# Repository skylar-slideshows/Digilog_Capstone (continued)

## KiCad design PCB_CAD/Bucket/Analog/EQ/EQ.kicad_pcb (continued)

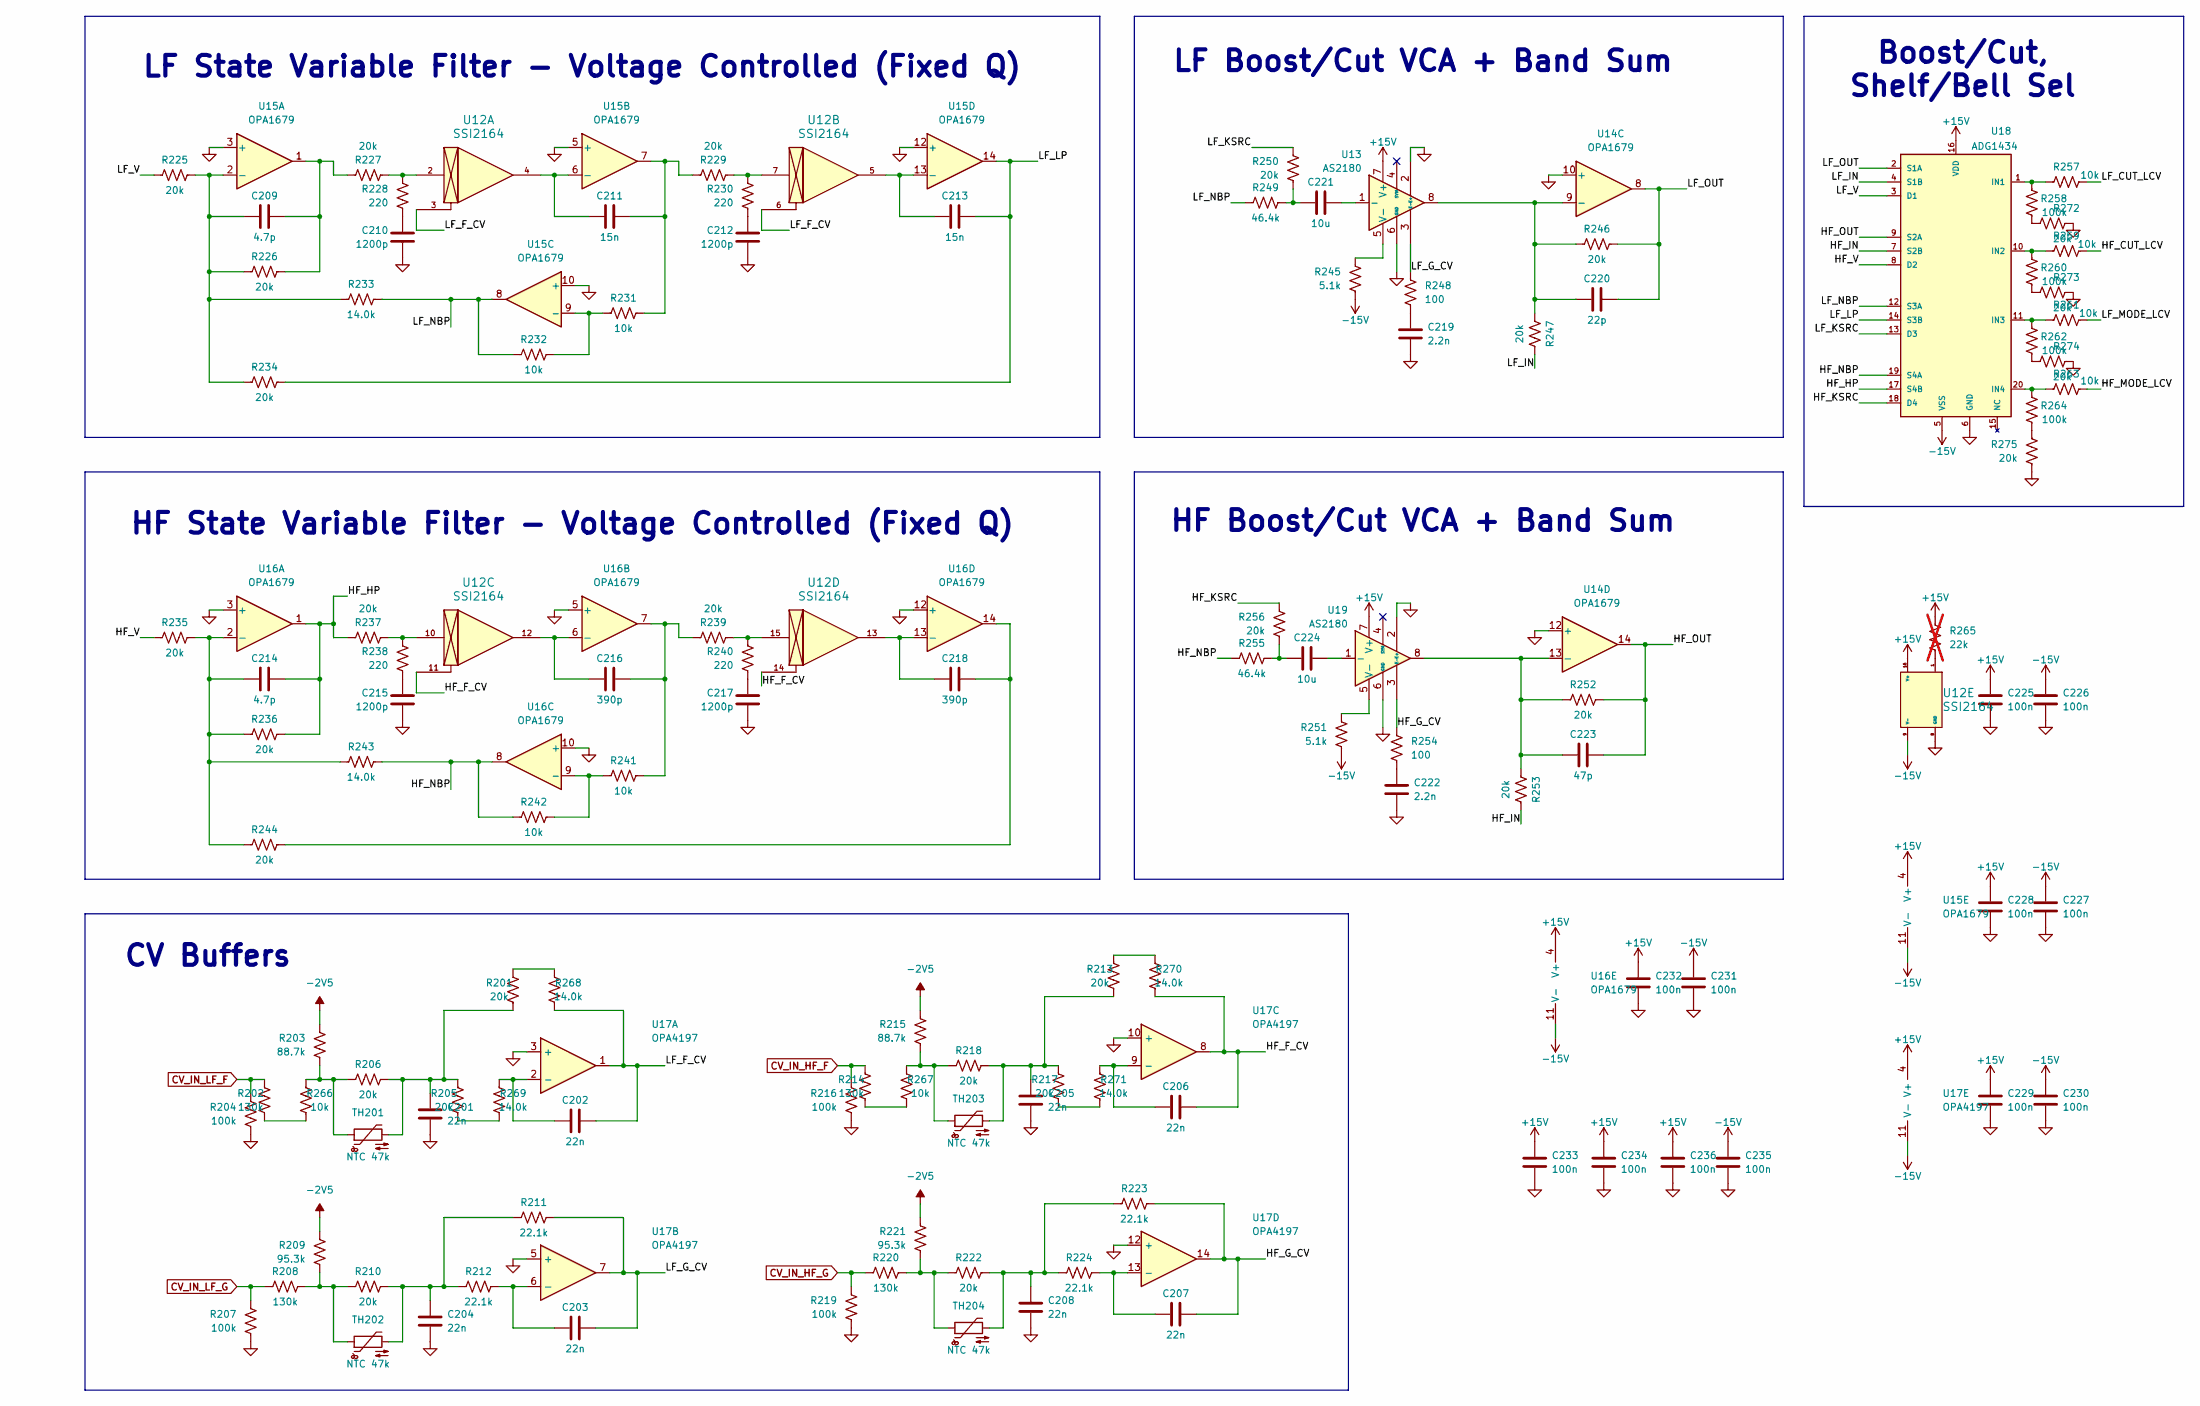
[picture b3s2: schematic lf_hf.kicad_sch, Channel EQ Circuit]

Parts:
C201, C202, C203, C204, C205, C206, C207, C208: 22n; C_Rect_L7.2mm_W2.5mm_P5.00mm; LCSC dnp
C209, C214: 4.7p; C_0603_1608Metric; LCSC C282071
C210, C212, C215, C217: 1200p; C_1206_3216Metric; LCSC C527278
C211, C213: 15n; C_Rect_L7.2mm_W2.5mm_P5.00mm; LCSC dnp
C216, C218: 390p; C_0603_1608Metric; LCSC C107050
C219, C222: 2.2n; C_0805_2012Metric; LCSC C107103
C220: 22p; C_0603_1608Metric; LCSC C105620
C221, C224: 10u; CP_Elec_6.3x5.4_Nichicon; LCSC C340735
C223: 47p; C_0603_1608Metric; LCSC C105622
C225, C226, C227, C228, C229, C230, C231, C232, C233, C234, C235, C236: 100n; C_0603_1608Metric; LCSC C1591
R201, R205, R206, R210, R213, R217, R218, R222, R225, R226, R227, R229, R234, R235, R236, R237, R239, R244, R246, R247, R250, R252, R253, R256, R272, R273, R274, R275: 20k; R_0603_1608Metric
R202, R208, R214, R220: 130k; R_0603_1608Metric
R203, R215: 88.7k; R_0603_1608Metric
R204, R207, R216, R219, R258, R260, R262, R264: 100k; R_0603_1608Metric
R209, R221: 95.3k; R_0603_1608Metric
R211, R212, R223, R224: 22.1k; R_0603_1608Metric
R228, R230, R238, R240: 220; R_0603_1608Metric
R231, R232, R241, R242, R257, R259, R261, R263, R266, R267: 10k; R_0603_1608Metric
R233, R243, R268, R269, R270, R271: 14.0k; R_0603_1608Metric
R245, R251: 5.1k; R_0603_1608Metric
R248, R254: 100; R_0603_1608Metric
R249, R255: 46.4k; R_0603_1608Metric
R265: 22k; R_0603_1608Metric; not fitted
TH201, TH202, TH203, TH204: NTC 47k; R_Axial_DIN0207_L6.3mm_D2.5mm_P2.54mm_Vertical; MPN NTCLE100E3473JB0; LCSC dnp
U12: SSI2164; SOIC-16_3.9x9.9mm_Pitch1.27mm; LCSC dnp
U13, U19: AS2180; SOIC-8-1EP_3.9x4.9mm_P1.27mm_EP2.29x3mm_ThermalVias; LCSC dnp
U14, U15, U16: OPA1679; SOIC-14_3.9x8.7mm_P1.27mm; LCSC C2057264
U17: OPA4197; SOIC-14_3.9x8.7mm_P1.27mm; LCSC C2058532
U18: ADG1434; TSSOP-20_4.4x6.5mm_P0.65mm; LCSC C408906

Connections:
+15V: C225.1, C228.1, C229.1, C232.1, C233.1, C234.1, C236.1, R265.1, U12.16 (V+), U13.7 (V+), U15.4 (V+), U16.4 (V+), U17.4 (V+), U18.16 (VDD), U19.7 (V+); also elsewhere on the board
-2V5: R203.1, R209.1, R215.1, R221.1; also elsewhere on the board
-15V: C226.1, C227.1, C230.1, C231.1, C235.1, R245.2, R251.2, U12.9 (V-), U15.11 (V-), U16.11 (V-), U17.11 (V-), U18.5 (VSS); also elsewhere on the board
/LF_HF/HF_CUT_LCV: R259.2
/LF_HF/HF_F_CV: C206.2, R270.2, U12.11, U12.14, U17.8
/LF_HF/HF_G_CV: C207.2, R223.2, R254.1, U17.14, U19.3 (E-)
/LF_HF/HF_HP: C214.2, R236.2, R237.1, U16.1, U18.17 (S4B)
/LF_HF/HF_IN: R253.2, U18.7 (S2B)
/LF_HF/HF_KSRC: R256.1, U18.18 (D4)
/LF_HF/HF_MODE_LCV: R263.2
/LF_HF/HF_NBP: R242.1, R243.2, R255.1, U16.8, U18.19 (S4A)
/LF_HF/HF_OUT: C223.2, R252.2, U14.14, U18.9 (S2A)
/LF_HF/HF_V: R235.1, U18.8 (D2)
/LF_HF/LF_CUT_LCV: R257.2
/LF_HF/LF_F_CV: C202.2, R268.2, U12.3, U12.6, U17.1
/LF_HF/LF_G_CV: C203.2, R211.2, R248.1, U13.3 (E-), U17.7
/LF_HF/LF_IN: R247.2, U18.4 (S1B)
/LF_HF/LF_KSRC: R250.1, U18.13 (D3)
/LF_HF/LF_LP: C213.2, R234.2, U15.14, U18.14 (S3B)
/LF_HF/LF_MODE_LCV: R261.2
/LF_HF/LF_NBP: R232.1, R233.2, R249.1, U15.8, U18.12 (S3A)
/LF_HF/LF_OUT: C220.2, R246.2, U14.8, U18.2 (S1A)
/LF_HF/LF_V: R225.1, U18.3 (D1)
CV_IN_HF_F: R214.1, R216.1
CV_IN_HF_G: R219.1, R220.1
CV_IN_LF_F: R202.1, R204.1
CV_IN_LF_G: R207.1, R208.1
GND: C201.2, C204.2, C205.2, C208.2, C210.2, C212.2, C215.2, C217.2, C219.2, C222.2, C225.2, C226.2, C227.2, C228.2, C229.2, C230.2, C231.2, C232.2, C233.2, C234.2, C235.2, C236.2, R204.2, R207.2, R216.2, R219.2, R272.2, R273.2, R274.2, R275.2, U12.8 (GND), U13.2 (E+), U13.6 (GND), U14.10 (+), U14.12 (+), U15.3 (+), U15.5 (+), U15.10 (+), U15.12 (+), U16.3 (+), U16.5 (+), U16.10 (+), U16.12 (+), U17.3 (+), U17.5 (+), U17.10 (+), U17.12 (+), U18.6 (GND), U19.2 (E+), U19.6 (GND); also elsewhere on the board
unnamed: C201.1, R201.1, R205.1, R206.2, TH201.2
unnamed: C204.1, R210.2, R211.1, R212.1, TH202.2
unnamed: C205.1, R213.1, R217.1, R218.2, TH203.2
unnamed: C208.1, R222.2, R223.1, R224.1, TH204.2
unnamed: C209.2, R226.2, R227.1, U15.1
unnamed: C210.1, R228.2
unnamed: C211.2, R229.1, R231.2, U15.7
unnamed: C212.1, R230.2
unnamed: C215.1, R238.2
unnamed: C216.2, R239.1, R241.2, U16.7
unnamed: C217.1, R240.2
unnamed: C218.2, R244.2, U16.14
unnamed: C219.1, R248.2
unnamed: C221.1, R249.2, R250.2
unnamed: C222.1, R254.2
unnamed: C224.1, R255.2, R256.2
unnamed: R201.2, R268.1
unnamed: R202.2, R266.1
unnamed: R203.2, R206.1, R266.2, TH201.1
unnamed: R205.2, R269.1
unnamed: R208.2, R209.2, R210.1, TH202.1
unnamed: R213.2, R270.1
unnamed: R214.2, R267.1
unnamed: R215.2, R218.1, R267.2, TH203.1
unnamed: R217.2, R271.1
unnamed: R220.2, R221.2, R222.1, TH204.1
unnamed: R227.2, R228.1, U12.2
unnamed: R229.2, R230.1, U12.7
unnamed: R237.2, R238.1, U12.10
unnamed: R239.2, R240.1, U12.15
unnamed: R258.2, R272.1
unnamed: R260.2, R273.1
unnamed: R262.2, R274.1
unnamed: R264.2, R275.1
unnamed: R265.2, U12.1
unnamed: C221.2, U13.1 (-)
unnamed: R245.1, U13.5 (V-)
unnamed: C220.1, R246.1, R247.1, U13.8, U14.9 (-)
unnamed: C223.1, R252.1, R253.1, U14.13 (-), U19.8
unnamed: C209.1, R225.2, R226.1, R233.1, R234.1, U15.2 (-)
unnamed: C211.1, U12.4, U15.6 (-)
unnamed: R231.1, R232.2, U15.9 (-)
unnamed: C213.1, U12.5, U15.13 (-)
unnamed: C214.1, R235.2, R236.1, R243.1, R244.1, U16.2 (-)
unnamed: C216.1, U12.12, U16.6 (-)
unnamed: R241.1, R242.2, U16.9 (-)
unnamed: C218.1, U12.13, U16.13 (-)
unnamed: C202.1, R269.2, U17.2 (-)
unnamed: C203.1, R212.2, U17.6 (-)
unnamed: C206.1, R271.2, U17.9 (-)
unnamed: C207.1, R224.2, U17.13 (-)
unnamed: R257.1, R258.1, U18.1 (IN1)
unnamed: R259.1, R260.1, U18.10 (IN2)
unnamed: R261.1, R262.1, U18.11 (IN3)
unnamed: R263.1, R264.1, U18.20 (IN4)
unnamed: C224.2, U19.1 (-)
unnamed: R251.1, U19.5 (V-)

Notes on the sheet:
LF Boost/Cut VCA + Band Sum
LF State Variable Filter - Voltage Controlled (Fixed Q)
HF Boost/Cut VCA + Band Sum
HF State Variable Filter - Voltage Controlled (Fixed Q)
Boost/Cut, Shelf/Bell Sel
CV Buffers

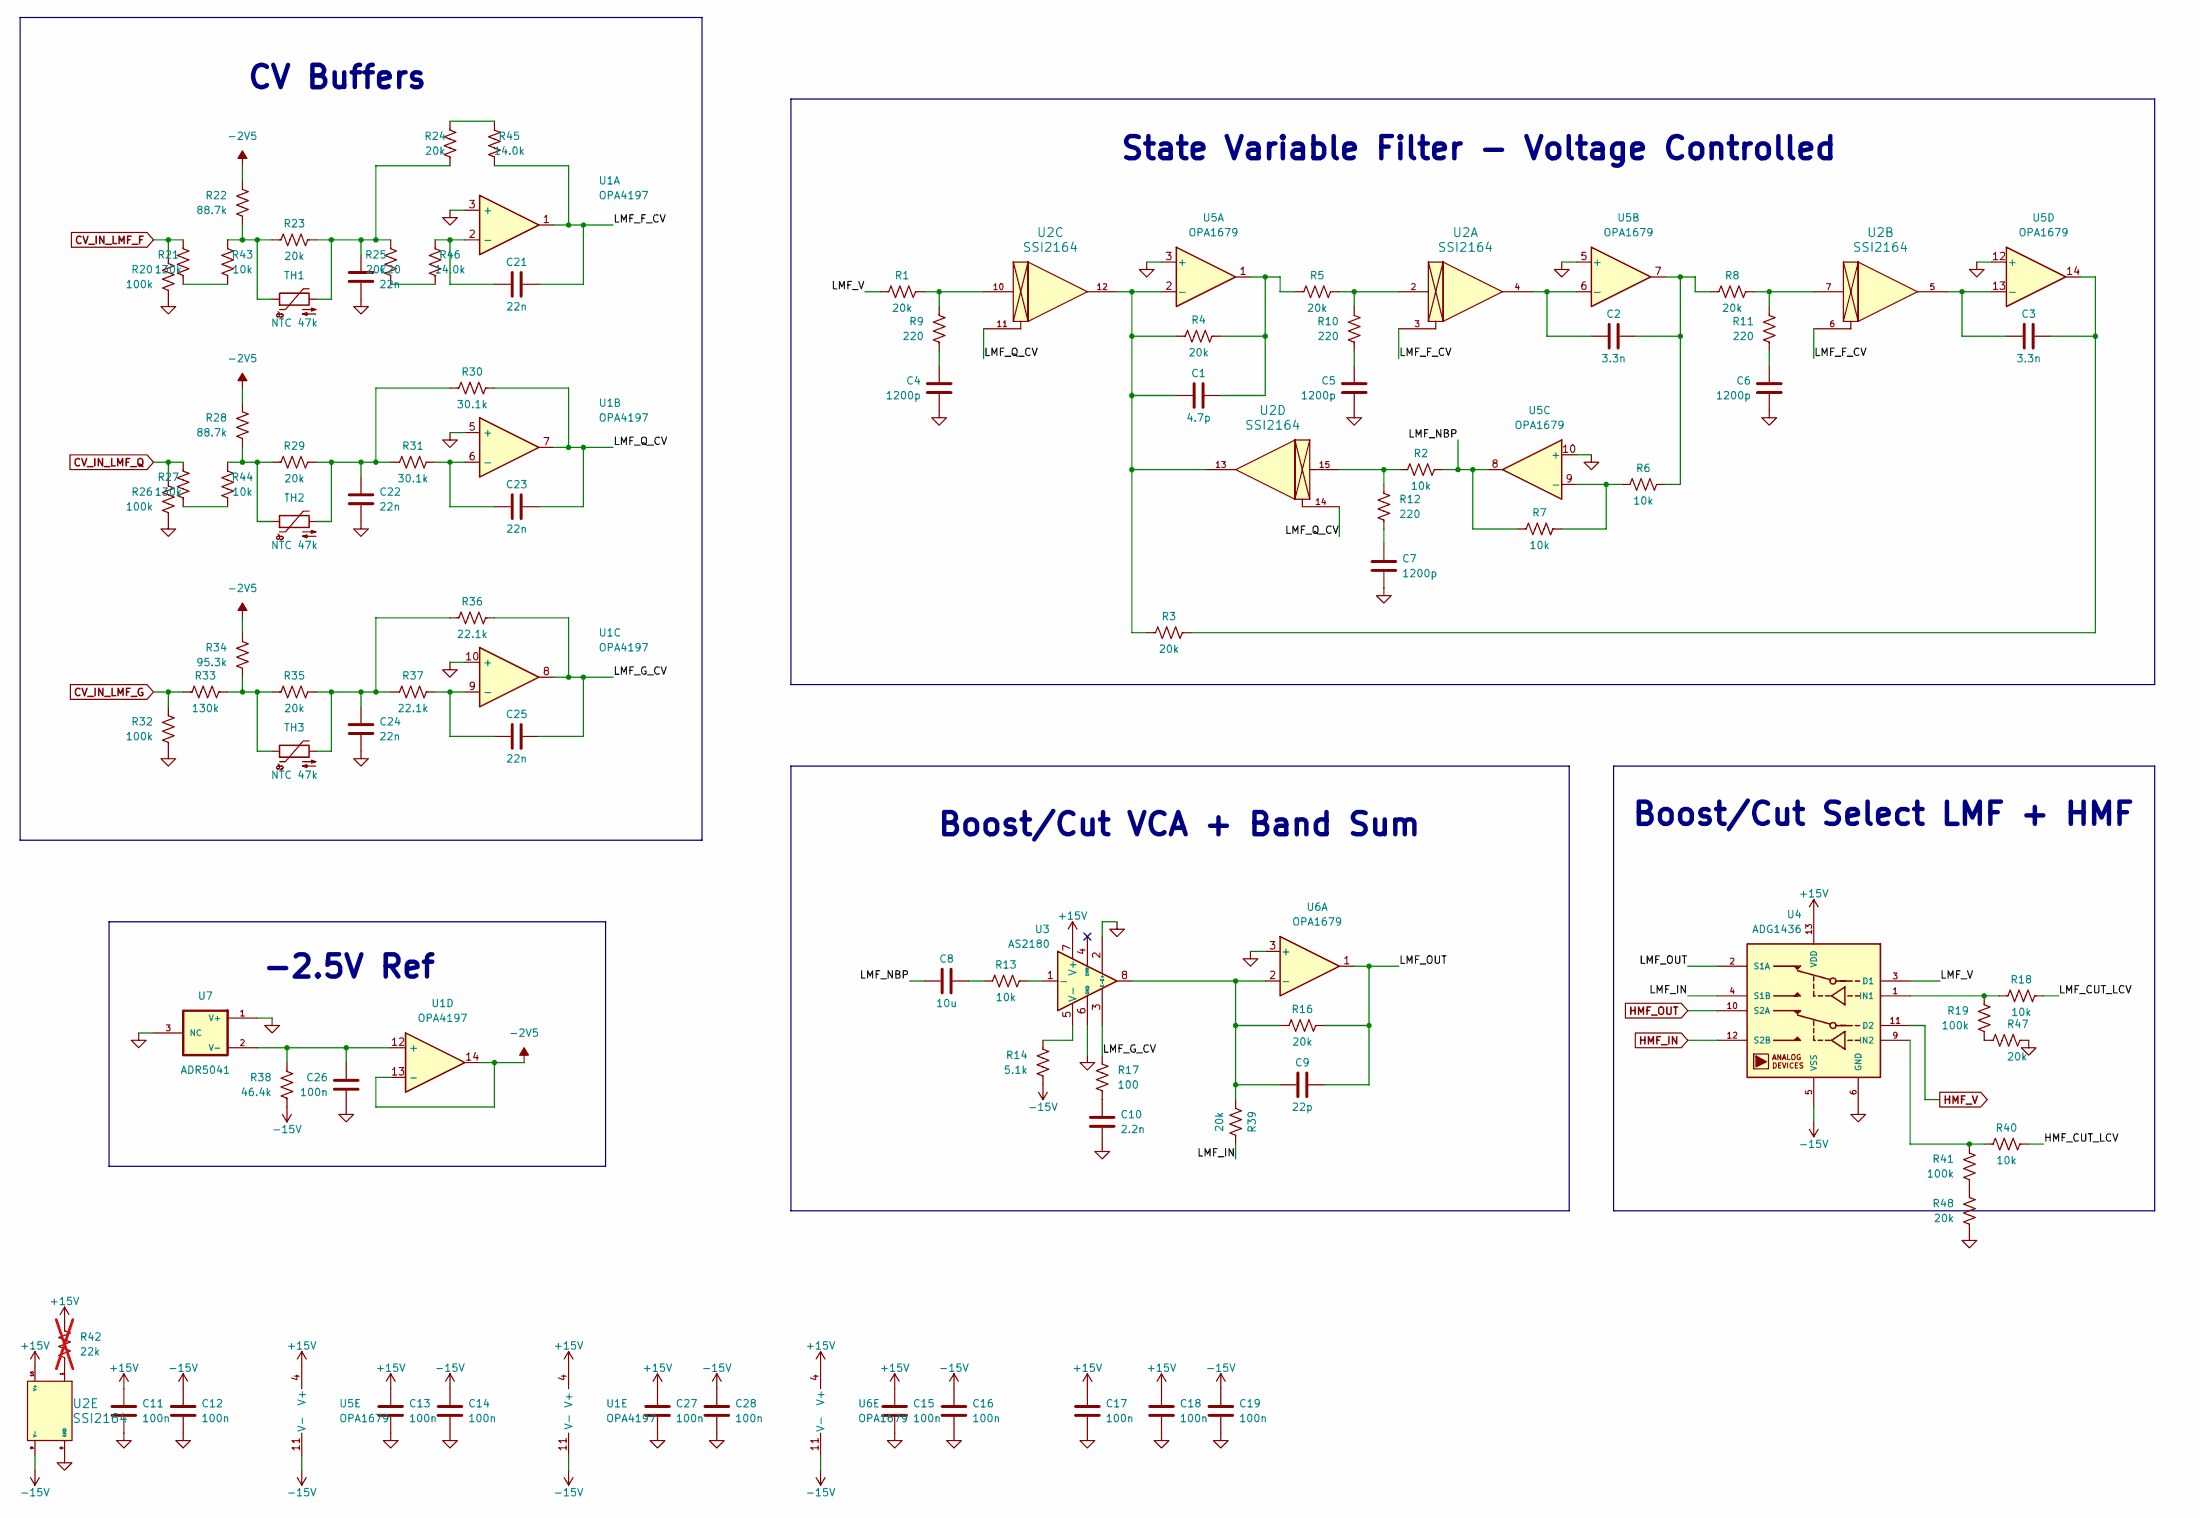
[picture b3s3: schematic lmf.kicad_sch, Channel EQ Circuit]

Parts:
C1: 4.7p; C_0603_1608Metric; LCSC C282071
C2, C3: 3.3n; C_0603_1608Metric; LCSC C107048
C4, C5, C6, C7: 1200p; C_1206_3216Metric; LCSC C527278
C8: 10u; CP_Elec_6.3x5.4_Nichicon; LCSC C340735
C9: 22p; C_0603_1608Metric; LCSC C105620
C10: 2.2n; C_0805_2012Metric; LCSC C107103
C11, C12, C13, C14, C15, C16, C17, C18, C19, C27, C28: 100n; C_0603_1608Metric; LCSC C1591
C20, C21, C22, C23, C24, C25: 22n; C_Rect_L7.2mm_W2.5mm_P5.00mm; LCSC dnp
C26: 100n; C_0603_1608Metric; LCSC C1590
R1, R3, R4, R5, R8, R16, R23, R24, R25, R29, R35, R39, R47, R48: 20k; R_0603_1608Metric
R2, R6, R7, R13, R18, R40, R43, R44: 10k; R_0603_1608Metric
R9, R10, R11, R12: 220; R_0603_1608Metric
R14: 5.1k; R_0603_1608Metric
R17: 100; R_0603_1608Metric
R19, R20, R26, R32, R41: 100k; R_0603_1608Metric
R21, R27, R33: 130k; R_0603_1608Metric
R22, R28: 88.7k; R_0603_1608Metric
R30, R31: 30.1k; R_0603_1608Metric
R34: 95.3k; R_0603_1608Metric
R36, R37: 22.1k; R_0603_1608Metric
R38: 46.4k; R_0603_1608Metric
R42: 22k; R_0603_1608Metric; not fitted
R45, R46: 14.0k; R_0603_1608Metric
TH1, TH2, TH3: NTC 47k; R_Axial_DIN0207_L6.3mm_D2.5mm_P2.54mm_Vertical; MPN NTCLE100E3473JB0; LCSC dnp
U1: OPA4197; SOIC-14_3.9x8.7mm_P1.27mm; LCSC C2058532
U2: SSI2164; SOIC-16_3.9x9.9mm_Pitch1.27mm; LCSC dnp
U3: AS2180; SOIC-8-1EP_3.9x4.9mm_P1.27mm_EP2.29x3mm_ThermalVias; LCSC dnp
U4: ADG1436; TSSOP16; LCSC C408899
U5, U6: OPA1679; SOIC-14_3.9x8.7mm_P1.27mm; LCSC C2057264
U7: ADR5041; SOT-23; MPN ADR5041ARTZ-R2; LCSC C659596

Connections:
+15V: C11.1, C13.1, C15.1, C17.1, C18.1, C27.1, R42.1, U1.4 (V+), U2.16 (V+), U3.7 (V+), U4.13 (VDD), U5.4 (V+), U6.4 (V+); also elsewhere on the board
-2V5: R22.1, R28.1, R34.1, U1.13 (-), U1.14; also elsewhere on the board
-15V: C12.1, C14.1, C16.1, C19.1, C28.1, R14.2, R38.2, U1.11 (V-), U2.9 (V-), U4.5 (VSS), U5.11 (V-), U6.11 (V-); also elsewhere on the board
/LMF/HMF_CUT_LCV: R40.2
/LMF/LMF_CUT_LCV: R18.2
/LMF/LMF_F_CV: C21.2, R45.2, U1.1, U2.3, U2.6
/LMF/LMF_G_CV: C25.2, R17.1, R36.2, U1.8, U3.3 (E-)
/LMF/LMF_IN: R39.2, U4.4 (S1B)
/LMF/LMF_NBP: C8.1, R2.2, R7.1, U5.8
/LMF/LMF_OUT: C9.2, R16.2, U4.2 (S1A), U6.1
/LMF/LMF_Q_CV: C23.2, R30.2, U1.7, U2.11, U2.14
/LMF/LMF_V: R1.1, U4.3 (D1)
CV_IN_LMF_F: R20.1, R21.1
CV_IN_LMF_G: R32.1, R33.1
CV_IN_LMF_Q: R26.1, R27.1
GND: C4.2, C5.2, C6.2, C7.2, C10.2, C11.2, C12.2, C13.2, C14.2, C15.2, C16.2, C17.2, C18.2, C19.2, C20.2, C22.2, C24.2, C26.2, C27.2, C28.2, R20.2, R26.2, R32.2, R47.2, R48.2, U1.3 (+), U1.5 (+), U1.10 (+), U2.8 (GND), U3.2 (E+), U3.6 (GND), U4.6 (GND), U5.3 (+), U5.5 (+), U5.10 (+), U5.12 (+), U6.3 (+), U7.1 (V+), U7.3 (NC); also elsewhere on the board
unnamed: C1.2, R4.2, R5.1, U5.1
unnamed: C2.2, R6.2, R8.1, U5.7
unnamed: C3.2, R3.2, U5.14
unnamed: C4.1, R9.2
unnamed: C5.1, R10.2
unnamed: C6.1, R11.2
unnamed: C7.1, R12.2
unnamed: C8.2, R13.1
unnamed: C10.1, R17.2
unnamed: C20.1, R23.2, R24.1, R25.1, TH1.2
unnamed: C22.1, R29.2, R30.1, R31.1, TH2.2
unnamed: C24.1, R35.2, R36.1, R37.1, TH3.2
unnamed: R1.2, R9.1, U2.10
unnamed: R5.2, R10.1, U2.2
unnamed: R8.2, R11.1, U2.7
unnamed: R2.1, R12.1, U2.15
unnamed: R19.2, R47.1
unnamed: R21.2, R43.1
unnamed: R22.2, R23.1, R43.2, TH1.1
unnamed: R24.2, R45.1
unnamed: R25.2, R46.1
unnamed: R27.2, R44.1
unnamed: R28.2, R29.1, R44.2, TH2.1
unnamed: R33.2, R34.2, R35.1, TH3.1
unnamed: R41.2, R48.1
unnamed: R42.2, U2.1
unnamed: C21.1, R46.2, U1.2 (-)
unnamed: C23.1, R31.2, U1.6 (-)
unnamed: C25.1, R37.2, U1.9 (-)
unnamed: C26.1, R38.1, U1.12 (+), U7.2 (V-)
unnamed: R13.2, U3.1 (-)
unnamed: R14.1, U3.5 (V-)
unnamed: R18.1, R19.1, U4.1 (IN1)
unnamed: R40.1, R41.1, U4.9 (IN2)
unnamed: C1.1, R3.1, R4.1, U2.12, U2.13, U5.2 (-)
unnamed: C2.1, U2.4, U5.6 (-)
unnamed: R6.1, R7.2, U5.9 (-)
unnamed: C3.1, U2.5, U5.13 (-)
unnamed: C9.1, R16.1, R39.1, U3.8, U6.2 (-)

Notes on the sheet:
Boost/Cut Select LMF + HMF
Boost/Cut VCA + Band Sum
-2.5V Ref
State Variable Filter - Voltage Controlled
CV Buffers

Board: 2 copper layers, 274 parts (0 on the bottom side), 168 nets, no tracks yet.

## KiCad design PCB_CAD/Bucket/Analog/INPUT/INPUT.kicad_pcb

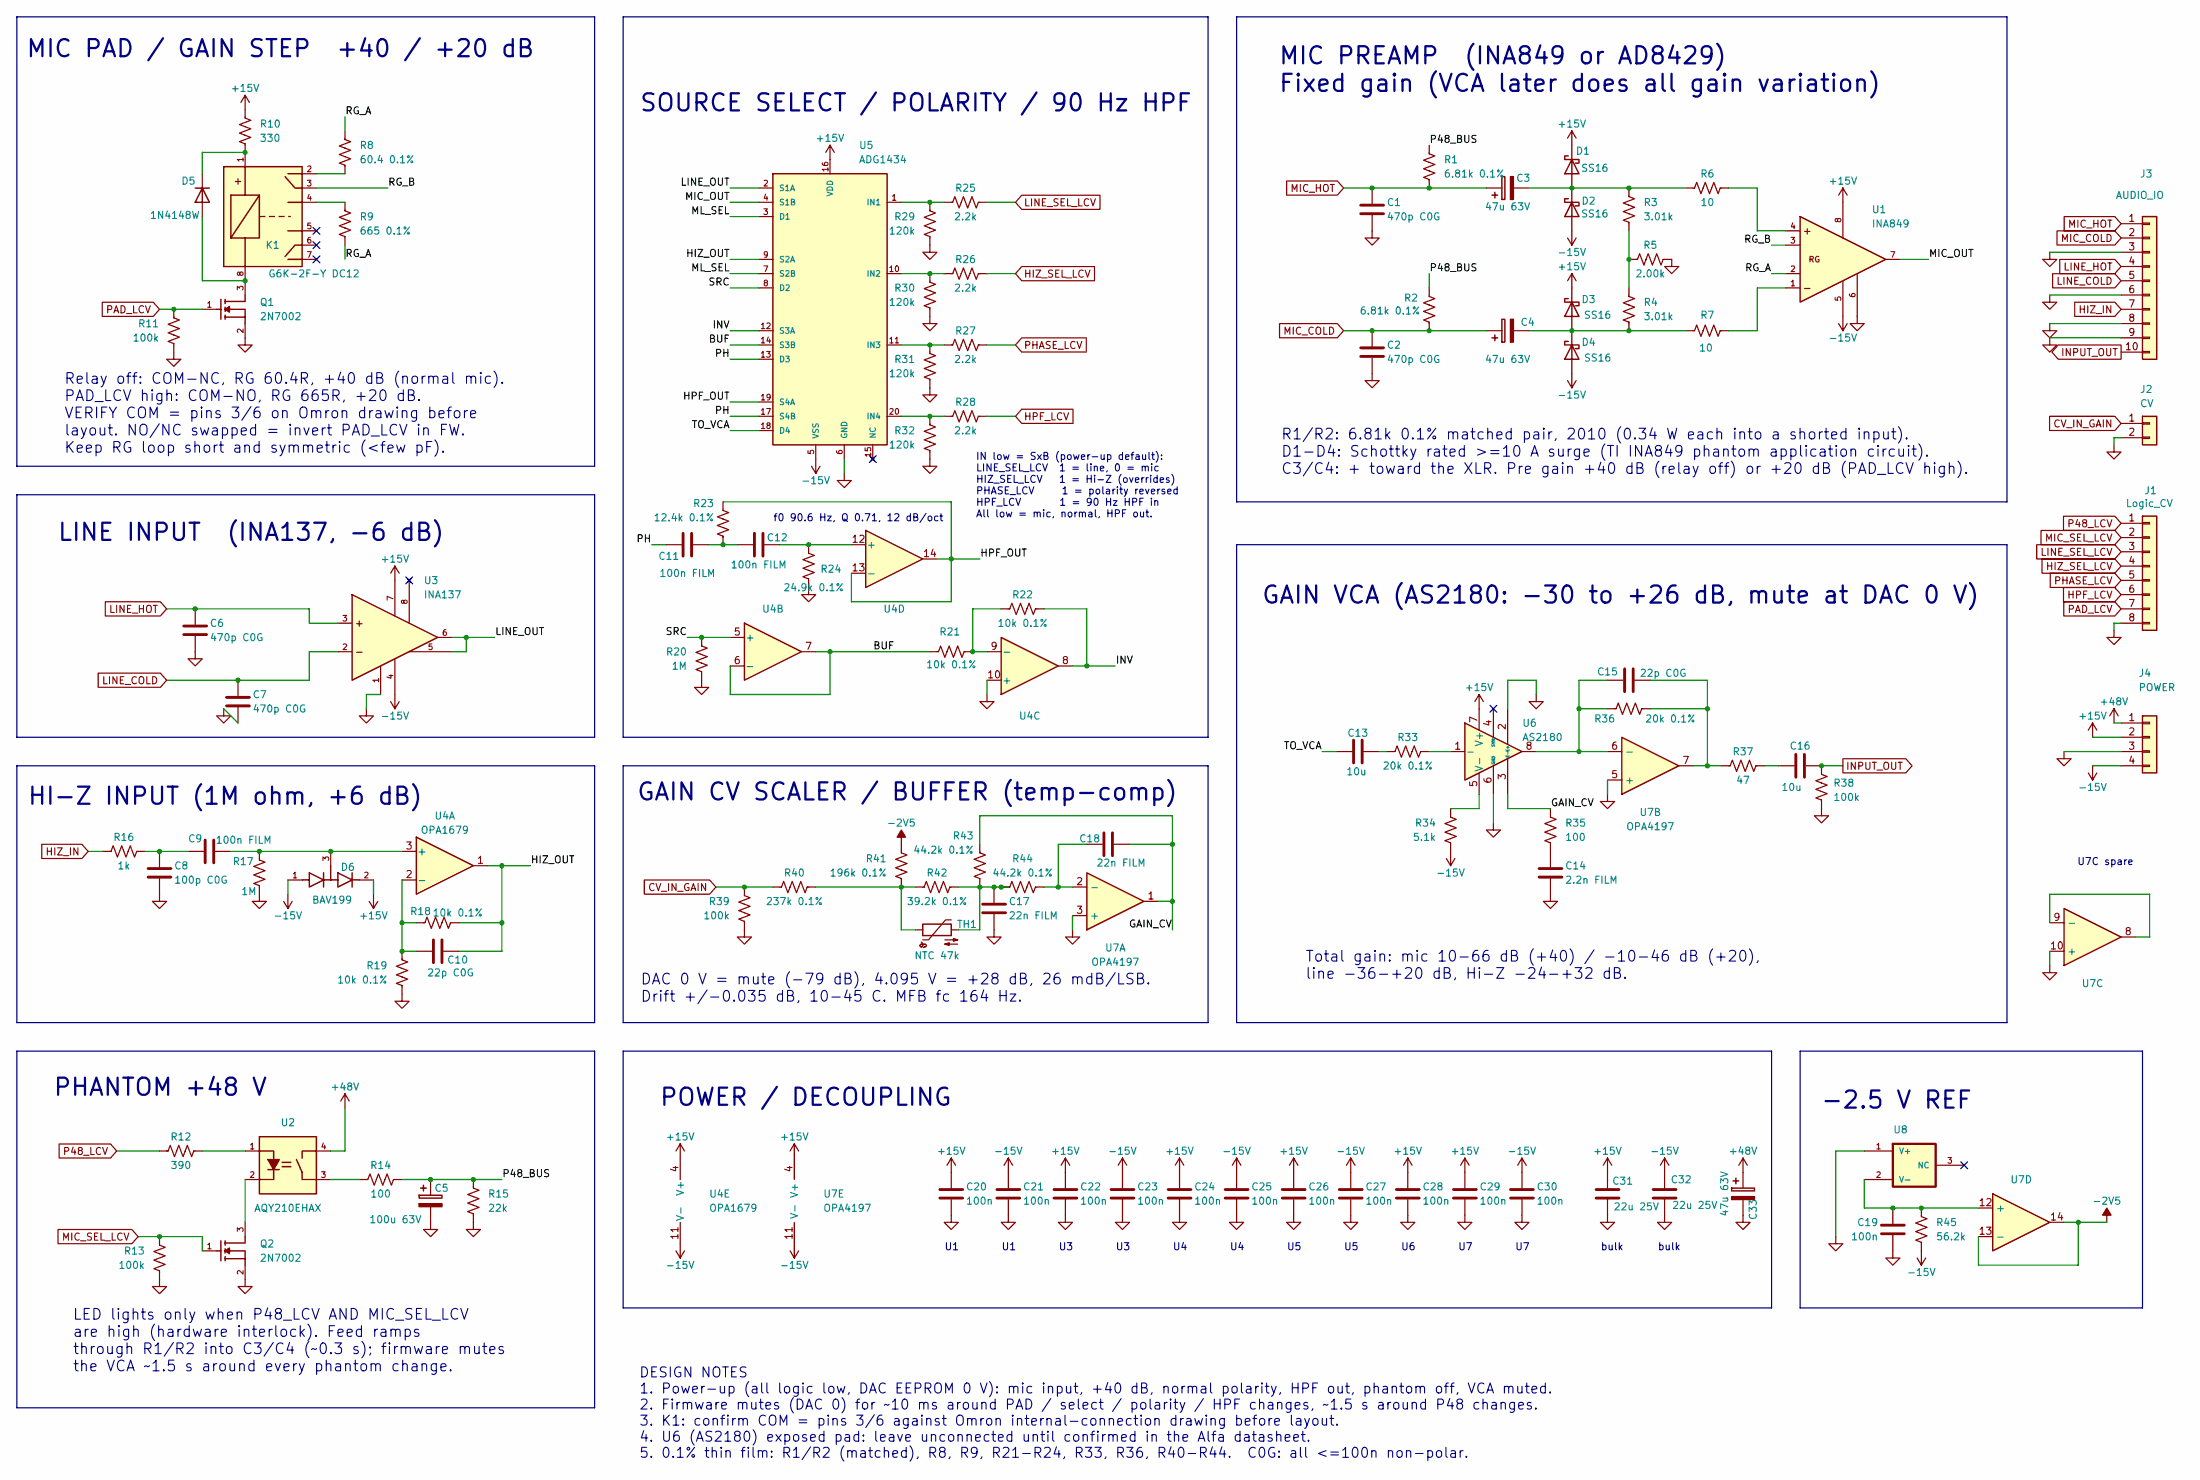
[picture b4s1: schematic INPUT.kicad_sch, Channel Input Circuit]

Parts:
C1, C2, C6, C7: 470p C0G; C_0603_1608Metric; LCSC C326973
C3, C4, C33: 47u 63V; CP_Elec_6.3x7.7; LCSC C48971005
C5: 100u 63V; CP_Elec_10x10.5; LCSC C51953411
C8: 100p C0G; C_0603_1608Metric; LCSC C14665
C9, C11, C12: 100n FILM; C_1812_4532Metric; LCSC C569829
C10, C15: 22p C0G; C_0603_1608Metric; LCSC C105620
C13, C16: 10u; C_0805_2012Metric; LCSC C1713
C14: 2.2n FILM; C_0603_1608Metric; LCSC C178417
C17, C18: 22n FILM; C_Rect_L7.2mm_W2.5mm_P5.00mm; LCSC _DNP_
C19, C20, C21, C22, C23, C24, C25, C26, C27, C28, C29, C30: 100n; C_0603_1608Metric; LCSC C1590
C31, C32: 22u 25V; C_1210_3225Metric; LCSC C21397
D1, D2, D3, D4: SS16; D_SMA; LCSC C2481
D5: 1N4148W; D_SOD-123; LCSC C2099
D6: BAV199; SOT-23; LCSC C145516
J1: Logic_CV; PinHeader_1x08_P2.54mm_Vertical
J2: CV; PinHeader_1x02_P2.54mm_Vertical; Part Number 1-0201FBV0T
J3: AUDIO_IO; PinHeader_1x10_P2.54mm_Vertical
J4: POWER; PinHeader_1x04_P2.54mm_Vertical
K1: G6K-2F-Y DC12; Relay_DPDT_Omron_G6K-2F-Y; LCSC C397194
Q1, Q2: 2N7002; SOT-23; LCSC C8545
R1, R2: 6.81k 0.1%; R_0603_1608Metric; LCSC C861538
R3, R4: 3.01k; R_0603_1608Metric; LCSC C137732
R5: 2.00k; R_0603_1608Metric; LCSC C318130
R6, R7: 10; R_0603_1608Metric; LCSC C217691
R8: 60.4 0.1%; R_0402_1005Metric; LCSC C852867
R9: 665 0.1%; R_0603_1608Metric; LCSC C861514
R10: 330; R_0603_1608Metric; LCSC C351654
R11, R13, R38, R39: 100k; R_0603_1608Metric; LCSC C122538
R12: 390; R_0603_1608Metric; LCSC C351650
R14, R35: 100; R_0603_1608Metric; LCSC C122970
R15: 22k; R_1206_3216Metric; LCSC C25654
R16: 1k; R_0603_1608Metric; LCSC C110776
R17, R20: 1M; R_0603_1608Metric; LCSC C234360
R18, R19, R21, R22: 10k 0.1%; R_0603_1608Metric; LCSC C95204
R23: 12.4k 0.1%; R_0603_1608Metric; LCSC C861102
R24: 24.9k 0.1%; R_0603_1608Metric; LCSC C667077
R25, R26, R27, R28: 2.2k; R_0603_1608Metric; LCSC C309092
R29, R30, R31, R32: 120k; R_0603_1608Metric; LCSC C136959
R33, R36: 20k 0.1%; R_0603_1608Metric; LCSC C190611
R34: 5.1k; R_0603_1608Metric; LCSC C122969
R37: 47; R_0603_1608Metric; LCSC C218045
R40: 237k 0.1%; R_0603_1608Metric; LCSC C217893
R41: 196k 0.1%; R_0402_1005Metric; LCSC C852585
R42: 39.2k 0.1%; R_0603_1608Metric; LCSC C861369
R43, R44: 44.2k 0.1%; R_0402_1005Metric; LCSC C705633
R45: 56.2k; R_0402_1005Metric; LCSC C36157922
TH1: NTC 47k; R_Axial_DIN0207_L6.3mm_D2.5mm_P2.54mm_Vertical; LCSC _DNP_
U1: INA849; MSOP-8-1EP_3x3mm_P0.65mm_EP1.68x1.88mm_ThermalVias; LCSC C4370731
U2: AQY210EHAX; SMDIP-4_W9.53mm; LCSC C24728
U3: INA137; SOIC-8-1EP_3.9x4.9mm_P1.27mm_EP2.29x3mm_ThermalVias; LCSC C2652878
U4: OPA1679; TSSOP-14_4.4x5mm_P0.65mm; LCSC C2057264
U5: ADG1434; TSSOP-20_4.4x6.5mm_P0.65mm; LCSC C408906
U6: AS2180; SOIC-8-1EP_3.9x4.9mm_P1.27mm_EP2.29x3mm_ThermalVias; LCSC _DNP_
U7: OPA4197; SOIC-14_3.9x8.7mm_P1.27mm; LCSC C2058532
U8: ADR5041; SOT-23; LCSC C2686108

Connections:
+15V: C20.1, C22.1, C24.1, C26.1, C28.1, C29.1, C31.1, D1.1 (K), D3.1 (K), D6.2 (K2), J4.2, R10.1, U1.8 (+VS), U3.7 (V+), U4.4 (V+), U5.16 (VDD), U6.7 (V+), U7.4 (V+)
+48V: C33.1 (+), J4.1, U2.4 (O)
-2V5: R41.1, U7.13 (-), U7.14
-15V: C21.1, C23.1, C25.1, C27.1, C30.1, C32.1, D2.2 (A), D4.2 (A), D6.1 (A1), J4.4, R34.2, R45.2, U1.5 (-VS), U3.4 (V-), U4.11 (V-), U5.5 (VSS), U7.11 (V-)
/BUF: R21.1, U4.6 (-), U4.7, U5.14 (S3B)
/GAIN_CV: C18.2, R35.1, R43.1, U6.3 (E-), U7.1
/HIZ_OUT: C10.2, R18.2, U4.1, U5.9 (S2A)
/HPF_OUT: R23.1, U4.13 (-), U4.14, U5.19 (S4A)
/INV: R22.2, U4.8, U5.12 (S3A)
/LINE_OUT: U3.5 (Sense), U3.6 (Out), U5.2 (S1A)
/MIC_OUT: U1.7 (OUT), U5.4 (S1B)
/ML_SEL: U5.3 (D1), U5.7 (S2B)
/P48_BUS: C5.1 (+), R1.1, R2.1, R14.2, R15.1
/PH: C11.1, U5.13 (D3), U5.17 (S4B)
/RG_A: R8.1, R9.2, U1.2 (RG)
/RG_B: K1.3 (COM1), U1.3 (RG)
/SRC: R20.1, U4.5 (+), U5.8 (D2)
/TO_VCA: C13.1, U5.18 (D4)
CV_IN_GAIN: J2.1, R39.1, R40.1
GND: C1.2, C2.2, C5.2 (-), C6.2, C7.2, C8.2, C14.2, C17.2, C19.2, C20.2, C21.2, C22.2, C23.2, C24.2, C25.2, C26.2, C27.2, C28.2, C29.2, C30.2, C31.2, C32.2, C33.2 (-), J1.8, J2.2, J3.3, J3.6, J3.8, J3.9, J4.3, Q1.2 (S), Q2.2 (S), R5.2, R11.2, R13.2, R15.2, R17.2, R19.2, R20.2, R24.2, R29.2, R30.2, R31.2, R32.2, R38.2, R39.2, U1.6 (REF), U3.1 (Ref), U4.10 (+), U5.6 (GND), U6.2 (E+), U6.6 (GND), U7.3 (+), U7.5 (+), U7.10 (+), U8.1 (V+)
HIZ_IN: J3.7, R16.1
HIZ_SEL_LCV: J1.4, R26.2
HPF_LCV: J1.6, R28.2
INPUT_OUT: C16.2, J3.10, R38.1
LINE_COLD: C7.1, J3.5, U3.2 (-In)
LINE_HOT: C6.1, J3.4, U3.3 (+In)
LINE_SEL_LCV: J1.3, R25.2
MIC_COLD: C2.1, C4.1 (+), J3.2, R2.2
MIC_HOT: C1.1, C3.1 (+), J3.1, R1.2
MIC_SEL_LCV: J1.2, Q2.1 (G), R13.1
unnamed: C3.2 (-), D1.2 (A), D2.1 (K), R3.1, R6.1
unnamed: C4.2 (-), D3.2 (A), D4.1 (K), R4.2, R7.1
unnamed: C8.1, C9.1, R16.2
unnamed: C11.2, C12.1, R23.2
unnamed: C13.2, R33.1
unnamed: C14.1, R35.2
unnamed: C15.2, R36.2, R37.1, U7.7
unnamed: C16.1, R37.2
unnamed: C17.1, R42.2, R43.2, R44.1, TH1.2
unnamed: D5.2 (A), K1.8 (-), Q1.3 (D)
unnamed: D5.1 (K), K1.1 (+), R10.2
unnamed: C9.2, D6.3 (K1A2), R17.1, U4.3 (+)
unnamed: K1.2 (NC1), R8.2
unnamed: K1.4 (NO1), R9.1
unnamed: Q2.3 (D), U2.2 (K)
unnamed: R3.2, R4.1, R5.1
unnamed: R14.1, U2.3 (O)
unnamed: R40.2, R41.2, R42.1, TH1.1
unnamed: R6.2, U1.4 (+IN)
unnamed: R7.2, U1.1 (-IN)
unnamed: R12.2, U2.1 (A)
unnamed: C10.1, R18.1, R19.1, U4.2 (-)
unnamed: R21.2, R22.1, U4.9 (-)
unnamed: C12.2, R24.1, U4.12 (+)
unnamed: R25.1, R29.1, U5.1 (IN1)
unnamed: R26.1, R30.1, U5.10 (IN2)
unnamed: R27.1, R31.1, U5.11 (IN3)
unnamed: R28.1, R32.1, U5.20 (IN4)
unnamed: R33.2, U6.1 (-)
unnamed: R34.1, U6.5 (V-)
unnamed: C18.1, R44.2, U7.2 (-)
unnamed: C15.1, R36.1, U6.8, U7.6 (-)
unnamed: U7.8, U7.9 (-)
unnamed: C19.1, R45.1, U7.12 (+), U8.2 (V-)
P48_LCV: J1.1, R12.1
PAD_LCV: J1.7, Q1.1 (G), R11.1
PHASE_LCV: J1.5, R27.2

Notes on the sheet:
DESIGN NOTES 1. Power-up (all logic low, DAC EEPROM 0 V): mic input, +40 dB, normal polarity, HPF out, phantom off, VCA muted. 2. Firmware mutes (DAC 0) for ~10 ms around PAD / select / polarity / HPF changes, ~1.5 s around P48 changes. 3. K1: confirm COM = pins 3/6 against Omron internal-connectio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
MIC PREAMP (INA849 or AD8429) Fixed gain (VCA later does all gain variation)
IN low = SxB (power-up default): LINE_SEL_LCV 1 = line, 0 = mic HIZ_SEL_LCV 1 = Hi-Z (overrides) PHASE_LCV 1 = polarity reversed HPF_LCV 1 = 90 Hz HPF in All low = mic, normal, HPF out.
PHANTOM +48 V
LED lights only when P48_LCV AND MIC_SEL_LCV are high (hardware interlock). Feed ramps through R1/R2 into C3/C4 (~0.3 s); firmware mutes the VCA ~1.5 s around every phantom change.
DAC 0 V = mute (-79 dB), 4.095 V = +28 dB, 26 mdB/LSB. Drift +/-0.035 dB, 10-45 C. MFB fc 164 Hz.
bulk
U7C spare
POWER / DECOUPLING
GAIN CV SCALER / BUFFER (temp-comp)
Total gain: mic 10-66 dB (+40) / -10-46 dB (+20), line -36-+20 dB, Hi-Z -24-+32 dB.
HI-Z INPUT (1M ohm, +6 dB)
Relay off: COM-NC, RG 60.4R, +40 dB (normal mic). PAD_LCV high: COM-NO, RG 665R, +20 dB. VERIFY COM = pins 3/6 on Omron drawing before layout. NO/NC swapped = invert PAD_LCV in FW. Keep RG loop short and symmetric (<few pF).
f0 90.6 Hz, Q 0.71, 12 dB/oct
LINE INPUT (INA137, -6 dB)
SOURCE SELECT / POLARITY / 90 Hz HPF
GAIN VCA (AS2180: -30 to +26 dB, mute at DAC 0 V)
-2.5 V REF
MIC PAD / GAIN STEP +40 / +20 dB
R1/R2: 6.81k 0.1% matched pair, 2010 (0.34 W each into a shorted input). D1-D4: Schottky rated >=10 A surge (TI INA849 phantom application circuit). C3/C4: + toward the XLR. Pre gain +40 dB (relay off) or +20 dB (PAD_LCV high).

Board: 4 copper layers, 100 parts (4 on the bottom side), 67 nets, no tracks yet.

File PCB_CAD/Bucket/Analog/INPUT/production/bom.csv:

Designator,Footprint,Quantity,Value,LCSC Part #
"C1, C2, C6, C7",0603,4,470p C0G,C326973
"C10, C15",0603,2,22p C0G,C105620
"C11, C12, C9",1812,3,100n FILM,C569829
"C13, C16",0805,2,10u,C1713
C14,0603,1,2.2n FILM,C178417
"C17, C18",C_Rect_L7.2mm_W2.5mm_P5.00mm,2,22n FILM,_DNP_
"C19, C20, C21, C22, C23, C24, C25, C26, C27, C28, C29, C30",0603,12,100n,C1590
"C3, C33, C4",CP_Elec_6.3x7.7,3,47u 63V,C48971005
"C31, C32",1210,2,22u 25V,C21397
C5,CP_Elec_10x10.5,1,100u 63V,C51953411
C8,0603,1,100p C0G,C14665
"D1, D2, D3, D4",D_SMA,4,SS16,C2481
D5,D_SOD-123,1,1N4148W,C2099
D6,SOT-23,1,BAV199,C145516
J1,PinHeader_1x08_P2.54mm_Vertical,1,Logic_CV,
J2,PinHeader_1x02_P2.54mm_Vertical,1,CV,
J3,PinHeader_1x10_P2.54mm_Vertical,1,AUDIO_IO,
J4,PinHeader_1x04_P2.54mm_Vertical,1,POWER,
K1,Relay_DPDT_Omron_G6K-2F-Y,1,G6K-2F-Y DC12,C397194
"Q1, Q2",SOT-23,2,2N7002,C8545
"R1, R2",0603,2,6.81k 0.1%,C861538
R10,0603,1,330,C351654
"R11, R13, R38, R39",0603,4,100k,C122538
R12,0603,1,390,C351650
"R14, R35",0603,2,100,C122970
R15,1206,1,22k,C25654
R16,0603,1,1k,C110776
"R17, R20",0603,2,1M,C234360
"R18, R19, R21, R22",0603,4,10k 0.1%,C95204
R23,0603,1,12.4k 0.1%,C861102
R24,0603,1,24.9k 0.1%,C667077
"R25, R26, R27, R28",0603,4,2.2k,C309092
"R29, R30, R31, R32",0603,4,120k,C136959
"R3, R4",0603,2,3.01k,C137732
"R33, R36",0603,2,20k 0.1%,C190611
R34,0603,1,5.1k,C122969
R37,0603,1,47,C218045
R40,0603,1,237k 0.1%,C217893
R41,0402,1,196k 0.1%,C852585
R42,0603,1,39.2k 0.1%,C861369
"R43, R44",0402,2,44.2k 0.1%,C705633
R45,0402,1,56.2k,C36157922
R5,0603,1,2.00k,C318130
"R6, R7",0603,2,10,C217691
R8,0402,1,60.4 0.1%,C852867
R9,0603,1,665 0.1%,C861514
TH1,R_Axial_DIN0207_L6.3mm_D2.5mm_P2.54mm_Vertical,1,NTC 47k,_DNP_
U1,MSOP-8-1EP_3x3mm_P0.65mm_EP1.68x1.88mm_ThermalVias,1,INA849,C4370731
U2,SMDIP-4_W9.53mm,1,AQY210EHAX,C24728
U3,SOIC-8-1EP_3.9x4.9mm_P1.27mm_EP2.29x3mm_ThermalVias,1,INA137,C2652878
U4,TSSOP-14_4.4x5mm_P0.65mm,1,OPA1679,C2057264
U5,TSSOP-20_4.4x6.5mm_P0.65mm,1,ADG1434,C408906
U6,SOIC-8-1EP_3.9x4.9mm_P1.27mm_EP2.29x3mm_ThermalVias,1,AS2180,_DNP_
U7,SOIC-14_3.9x8.7mm_P1.27mm,1,OPA4197,C2058532
U8,SOT-23,1,ADR5041,C2686108
